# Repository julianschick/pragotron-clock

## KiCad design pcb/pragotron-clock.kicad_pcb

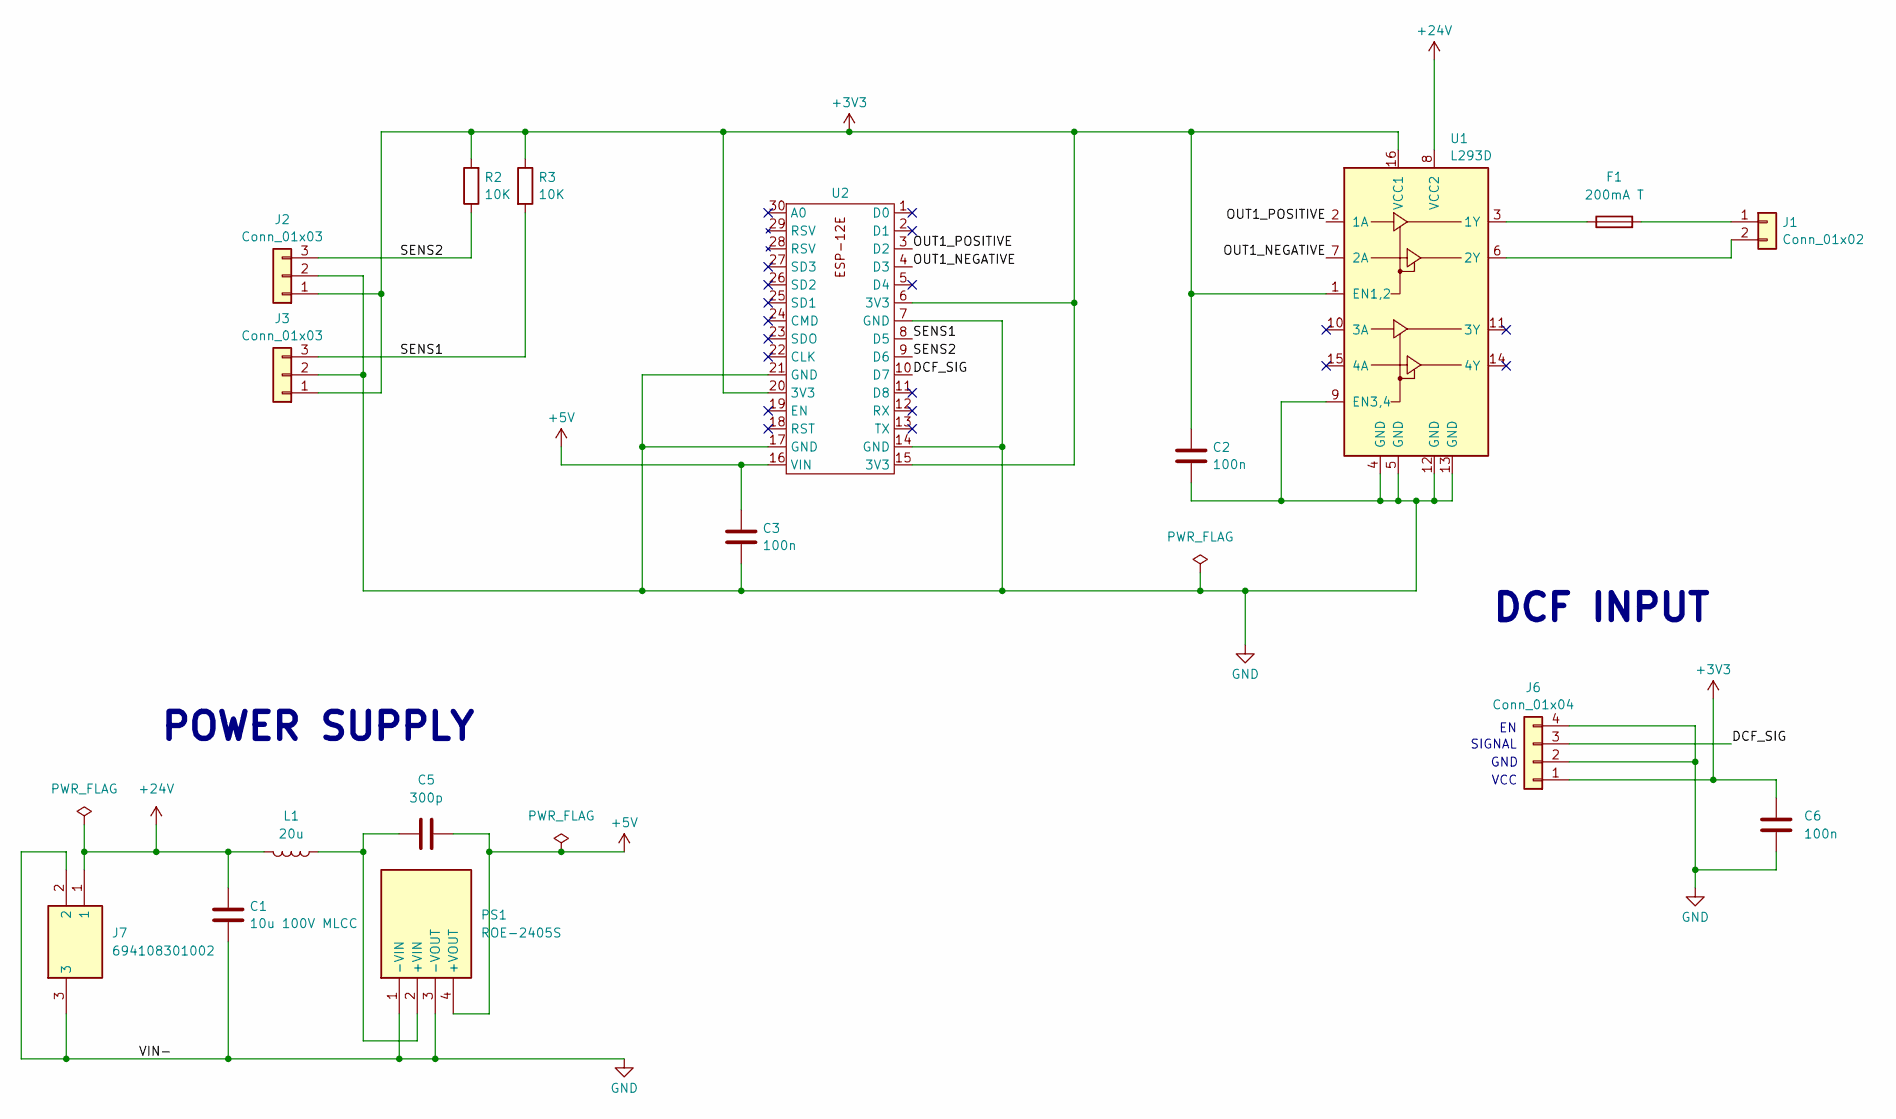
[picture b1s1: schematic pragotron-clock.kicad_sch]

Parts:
C1: 10u 100V MLCC; C_Rect_L7.0mm_W3.5mm_P5.00mm
C2, C3, C6: 100n; C_1206_3216Metric_Pad1.33x1.80mm_HandSolder
C5: 300p; C_1206_3216Metric_Pad1.33x1.80mm_HandSolder
F1: 200mA T; Fuse_1206_3216Metric_Pad1.42x1.75mm_HandSolder
J1: Conn_01x02; JST_XH_S2B-XH-A-1_1x02_P2.50mm_Horizontal
J2, J3: Conn_01x03; JST_XH_S3B-XH-A-1_1x03_P2.50mm_Horizontal
J6: Conn_01x04; DCF77
J7: 694108301002; Mouser Part Number 710-694108301002
L1: 20u; RLS226
PS1: ROE-2405S; ROE1205S; Mouser Part Number 919-ROE-2405S
R2, R3: 10K; R_1206_3216Metric_Pad1.30x1.75mm_HandSolder
U1: L293D; DIP-16_W7.62mm
U2: ESP8266_12E_DEVKIT

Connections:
+3V3: C2.1, C6.1, J2.1, J3.1, J6.1, R2.2, R3.1, U1.1 (EN1,2), U1.16 (VCC1), U2.6 (3V3), U2.15 (3V3), U2.20 (3V3)
+5V: C3.1, C5.1, PS1.4 (+VOUT), U2.16 (VIN)
+24V: C1.1, J7.1, L1.2, U1.8 (VCC2)
/DCF_SIG: J6.3, U2.10 (D7)
/OUT1_NEGATIVE: U1.7 (2A), U2.4 (D3)
/OUT1_POSITIVE: U1.2 (1A), U2.3 (D2)
/SENS1: J3.3, R3.2, U2.8 (D5)
/SENS2: J2.3, R2.1, U2.9 (D6)
GND: C1.2, C2.2, C3.2, C6.2, J2.2, J3.2, J6.2, J6.4, J7.2, J7.3, PS1.1 (-VIN), PS1.3 (-VOUT), U1.4 (GND), U1.5 (GND), U1.9 (EN3,4), U1.12 (GND), U1.13 (GND), U2.7 (GND), U2.14 (GND), U2.17 (GND), U2.21 (GND)
unnamed: F1.2, J1.1
unnamed: J1.2, U1.6 (2Y)
unnamed: C5.2, L1.1, PS1.2 (+VIN)
unnamed: F1.1, U1.3 (1Y)

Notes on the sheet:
GND
DCF INPUT
SIGNAL
POWER SUPPLY
VCC

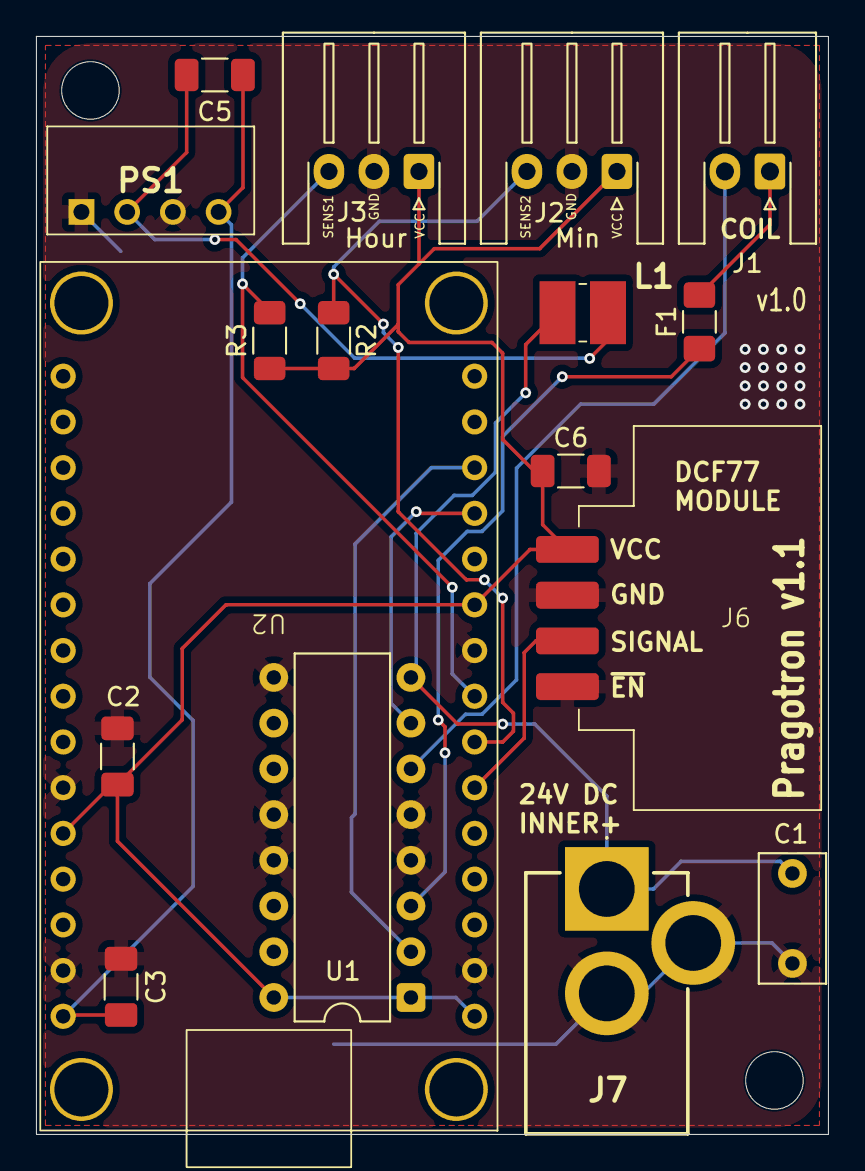
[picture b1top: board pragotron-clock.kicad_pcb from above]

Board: 2 copper layers, 44.0 x 61.0 mm, 17 parts (0 on the bottom side), 13 nets.

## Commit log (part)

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2026-01-18 initial
2026-02-22 control schematic
2026-02-28 add firmware
2026-03-08 firmware wip
2026-03-11 schematics+
2026-03-11 wip firmware
2026-03-16 firmware restructure
2026-03-17 firmware
2026-03-21 wip firmware and schematics
2026-03-21 schematic
2026-03-22 minification
2026-03-25 schematics finished
2026-03-28 firmware improvements
2026-03-31 schematics
2026-03-31 firmware sync improvements
2026-03-31 gerber v1.0
2026-04-01 fuse specification
